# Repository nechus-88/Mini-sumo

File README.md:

# VELOCISTA #
Un velocista realizado para competir en la LNR

# Este cuenta con: # 
* 1-Moodulo de TB6612FNG
* 1-Esp-32 38 pines
* 1-Motores N20 2000RPM 
* 1-Sensores qtr8a
* 1-Sensores sharp GP2Y0A02YK0F 20-150cm
* 1-Bateria 2S 7.4v 350mAh LiPo

# Dimensiones: #
* 70 X 120 (ancho x largo )

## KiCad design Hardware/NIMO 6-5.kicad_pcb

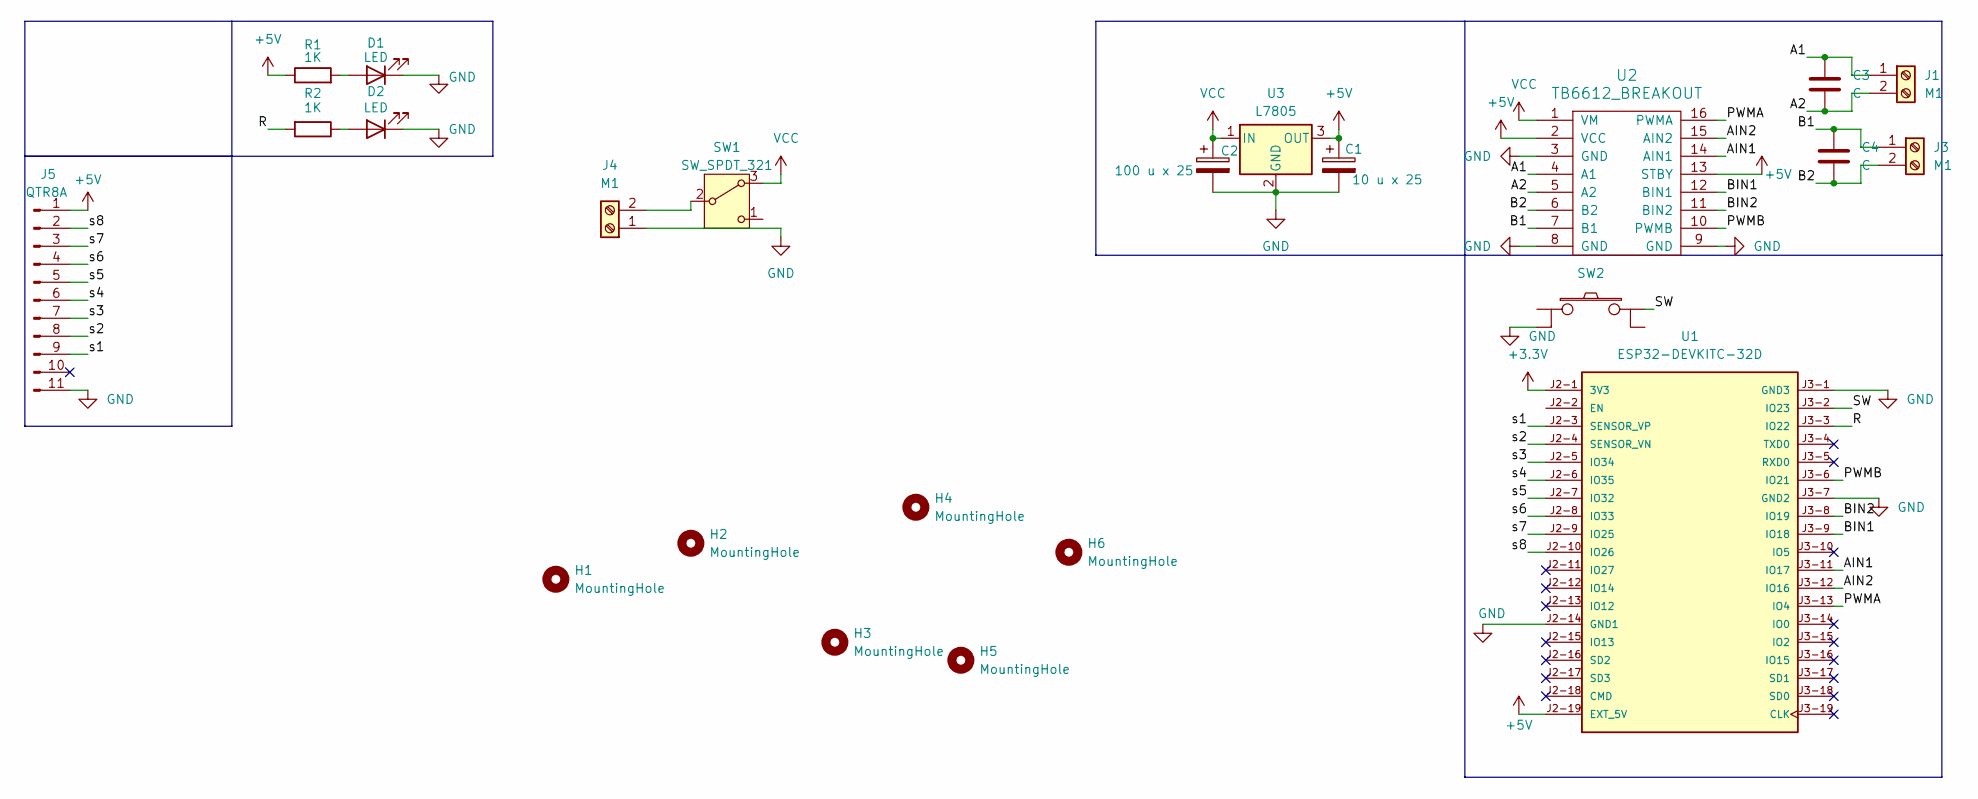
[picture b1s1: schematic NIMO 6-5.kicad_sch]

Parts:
C1: 10 u x 25; CP_Elec_8x6.2
C2: 100 u x 25; CP_Elec_6.3x5.4
C3, C4: C; C_0805_2012Metric
D1, D2: LED; LED_0805_2012Metric
H1, H2, H5, H6: MountingHole; MountingHole_3.2mm_M3
H3, H4: MountingHole; Pololu_Micro_Bracket_Wheel_42mms
J1, J3: M1; PinHeader_1x02_P2.54mm_Vertical
J4: M1; TerminalBlock_Altech_AK300-2_P5.00mm
J5: QTR8A; PinHeader_1x11_P2.54mm_Vertical
R1, R2: 1K; R_0805_2012Metric_Pad1.20x1.40mm_HandSolder
SW1: SW_SPDT_321; SW_SPDT_TH_Vertical
SW2: SW_PUSH; SW_PUSH_6mm_H5mm
U1: ESP32-DEVKITC-32D; MODULE_ESP32-DEVKITC-32D; PARTREV V4
U2: TB6612_BREAKOUT; TB6612_Breakout
U3: L7805; TO-263-2

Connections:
+3.3V: U1.J2-1 (3V3)
+5V: C1.1, J5.1, R1.1, U1.J2-19 (EXT_5V), U2.2 (VCC), U2.13 (STBY), U3.3 (OUT)
/A1: C3.2, J1.1, U2.4 (A1)
/A2: C3.1, J1.2, U2.5 (A2)
/AIN1: U1.J3-11 (IO17), U2.14 (AIN1)
/AIN2: U1.J3-12 (IO16), U2.15 (AIN2)
/B1: C4.2, J3.1, U2.7 (B1)
/B2: C4.1, J3.2, U2.6 (B2)
/BIN1: U1.J3-9 (IO18), U2.12 (BIN1)
/BIN2: U1.J3-8 (IO19), U2.11 (BIN2)
/PWMA: U1.J3-13 (IO4), U2.16 (PWMA)
/PWMB: U1.J3-6 (IO21), U2.10 (PWMB)
/R: R2.2, U1.J3-3 (IO22)
/SW: SW2.3, U1.J3-2 (IO23)
/s1: J5.9, U1.J2-3 (SENSOR_VP)
/s2: J5.8, U1.J2-4 (SENSOR_VN)
/s3: J5.7, U1.J2-5 (IO34)
/s4: J5.6, U1.J2-6 (IO35)
/s5: J5.5, U1.J2-7 (IO32)
/s6: J5.4, U1.J2-8 (IO33)
/s7: J5.3, U1.J2-9 (IO25)
/s8: J5.2, U1.J2-10 (IO26)
GND: C1.2, C2.2, D1.1 (K), D2.1 (K), J4.1, J5.11, SW2.2, U1.J2-14 (GND1), U1.J3-1 (GND3), U1.J3-7 (GND2), U2.3 (GND), U2.8 (GND), U2.9 (GND), U3.2 (GND)
unnamed: D1.2 (A), R1.2
unnamed: D2.2 (A), R2.1
unnamed: J4.2, SW1.2 (B)
VCC: C2.1, SW1.3 (A), U2.1 (VM), U3.1 (IN)

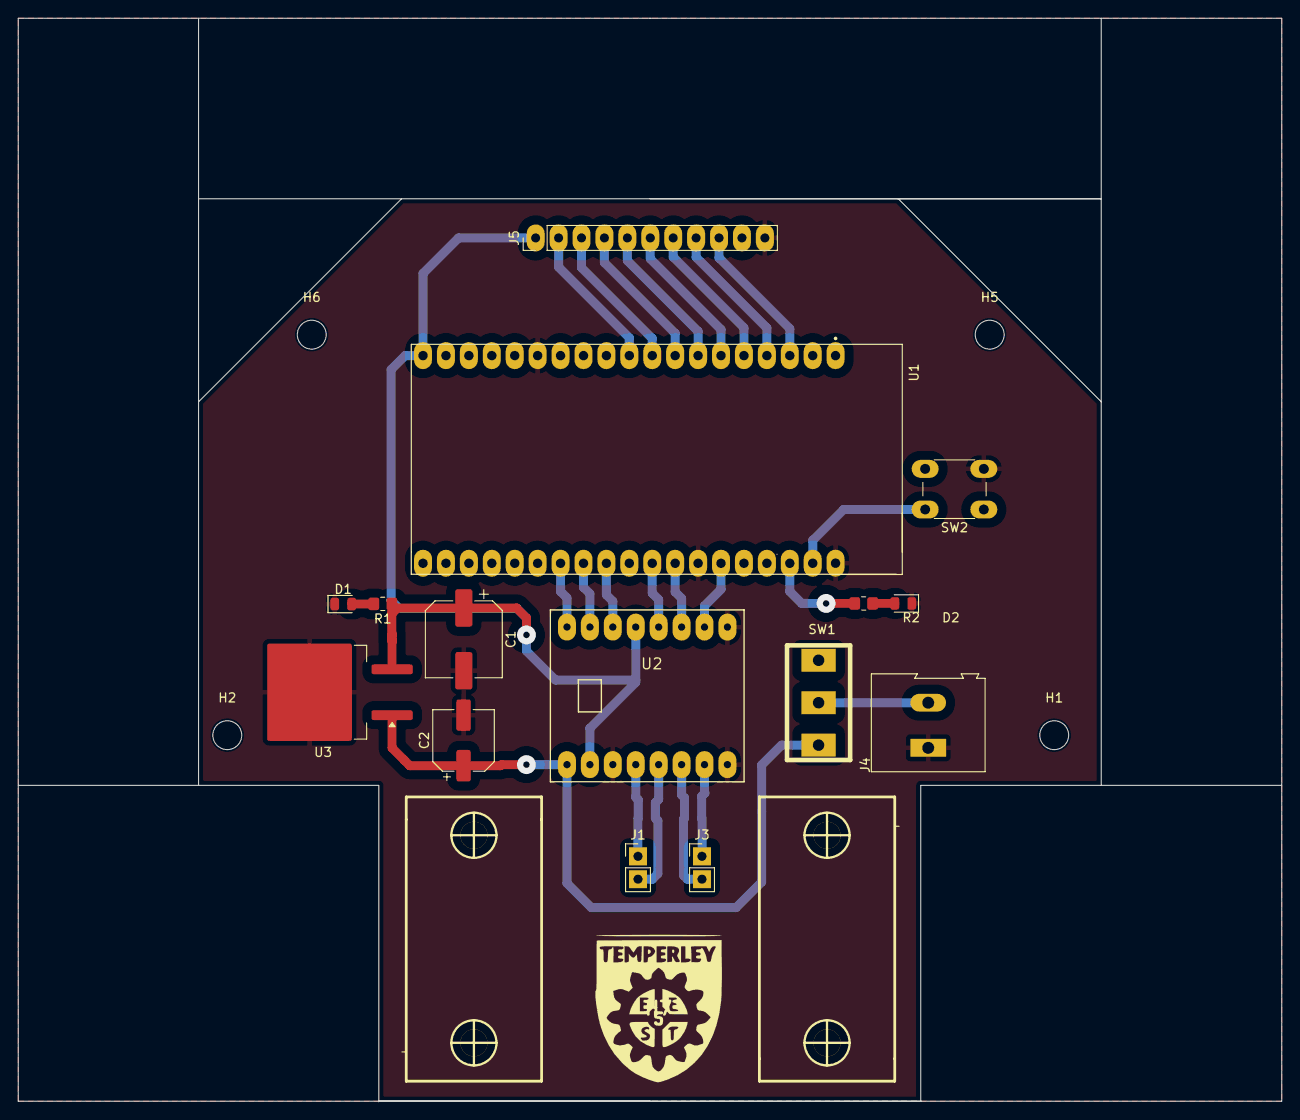
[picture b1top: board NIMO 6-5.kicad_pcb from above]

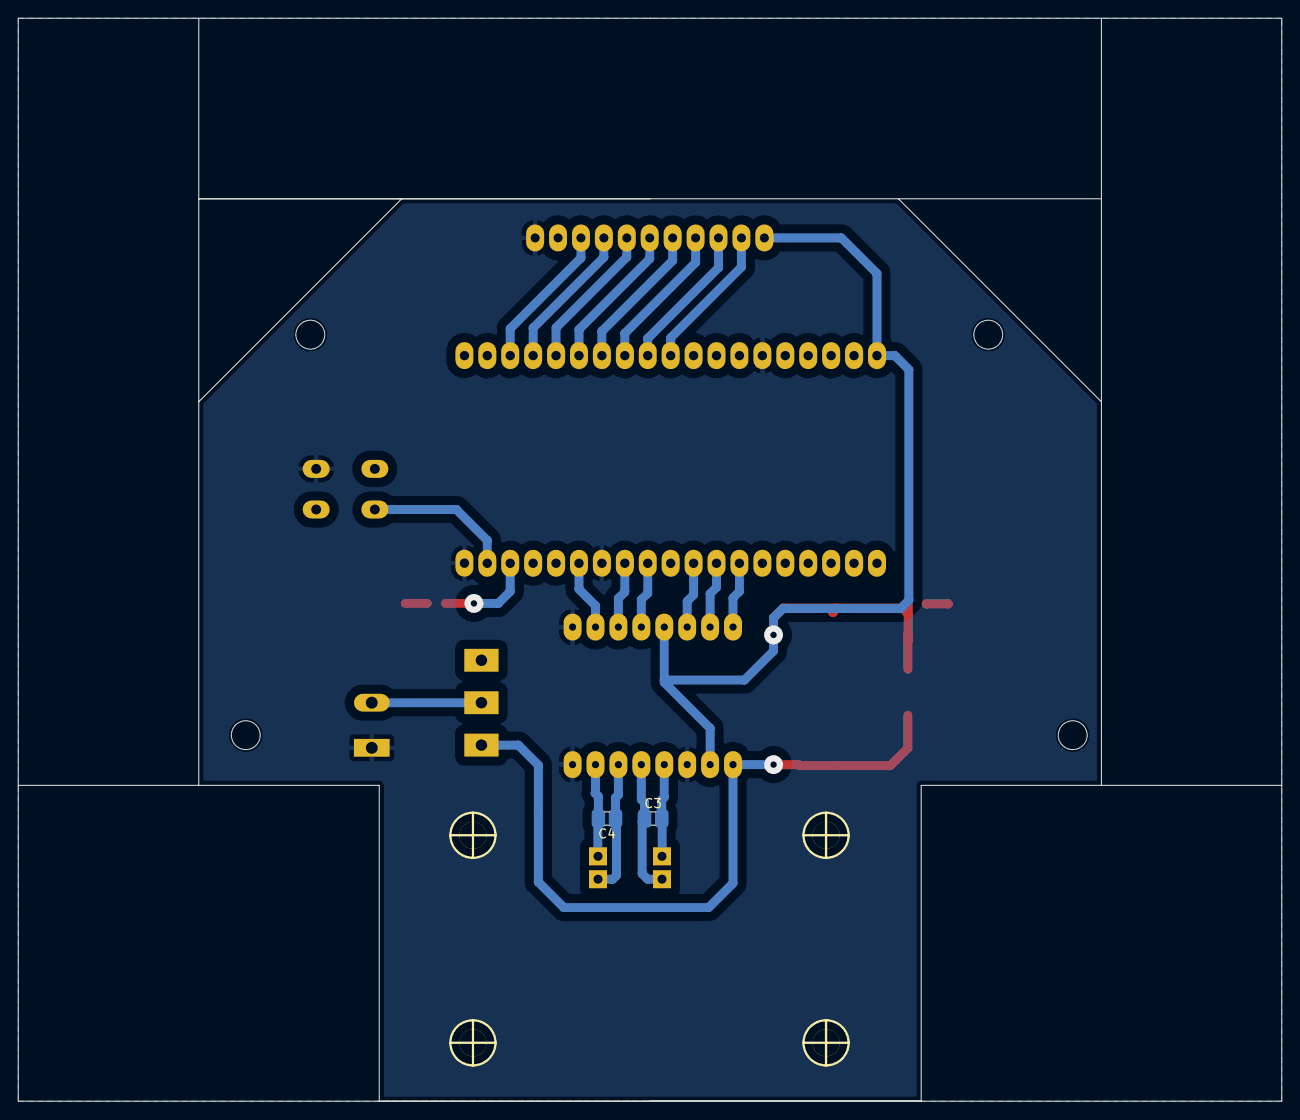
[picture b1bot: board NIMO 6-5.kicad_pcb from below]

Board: 2 copper layers, 140.0 x 120.0 mm, 24 parts (2 on the bottom side), 26 nets.

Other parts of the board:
H7: MountingHole; school

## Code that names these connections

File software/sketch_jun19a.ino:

#include <Arduino.h>
#include <QTRSensors.h>

#define NUM_SENSORS 8
uint8_t qtrPins[NUM_SENSORS] = {36, 39, 34, 35, 32, 33, 25, 26};
QTRSensors qtr;

#define BIN1 18
#define BIN2 19
#define AIN2 16
#define AIN1 17
#define PWMB 21
#define PWMA 4

#define LED_CALIBRACION 22
#define BOTON_CALIBRAR  23

#define PWM_FREQ  20000
#define PWM_RES   8
#define LINEA_NEGRA false

const int SETPOINT = 3500; // Centro de 8 sensores (0 a 7000)
float Kp = 0.32f;//0.31f
float Kd = 0.008f;//0.006f

float lastError = 0;
//float derivFiltrado = 0;
//const float ALPHA_D = 0.3f;

const int MAX_PWM       = 255;
const int VELOCIDAD_MAX = 255;
const int VELOCIDAD_MIN = 55;

unsigned long ultimoLoopUs = 0;

enum EstadoRobot { ESTADO_INICIAL, ESTADO_CALIBRANDO, ESTADO_LISTO, ESTADO_SIGUIENDO };
EstadoRobot estado = ESTADO_INICIAL;

void motorIzquierdo(int vel) {
  if (vel >= 0) { 
    digitalWrite(AIN1, LOW); 
  digitalWrite(AIN2, HIGH);
   }
  else { 
    digitalWrite(AIN1, HIGH);
     digitalWrite(AIN2, LOW);
      vel = -vel; }
  ledcWrite(PWMA, constrain(vel, 0, MAX_PWM));
}

void motorDerecho(int vel) {
  if (vel >= 0) {
     digitalWrite(BIN1, LOW);
      digitalWrite(BIN2, HIGH); 
      }
  else { 
    digitalWrite(BIN1, HIGH);
     digitalWrite(BIN2, LOW);
      vel = -vel;
       }
  ledcWrite(PWMB, constrain(vel, 0, MAX_PWM));
}

void motoresParar() {
  ledcWrite(PWMA, 0);
  ledcWrite(PWMB, 0);
}


void calibrar() {
  estado = ESTADO_CALIBRANDO;
  unsigned long tiempoInicio = millis();

  while (millis() - tiempoInicio < 12000) {
    qtr.calibrate();
    digitalWrite(LED_CALIBRACION, (millis() / 100) % 2); // Parpadeo
  }
  
  digitalWrite(LED_CALIBRACION, LOW);
  estado = ESTADO_LISTO;
  Serial.println("Calibración completa.");
}

void manejarBoton() {
  static bool presionadoPrev = HIGH;
  static unsigned long tiempoPresionado = 0;
  bool presionadoAct = digitalRead(BOTON_CALIBRAR);

  if (presionadoPrev == HIGH && presionadoAct == LOW) {
    tiempoPresionado = millis();
  }

  if (presionadoPrev == LOW && presionadoAct == HIGH) {
    unsigned long duracion = millis() - tiempoPresionado;

    if (duracion > 2000) { // +2s: Calibrar
      calibrar();
    } else if (duracion > 50) { // Click corto: Arrancar/Parar
      if (estado == ESTADO_LISTO) {
        estado = ESTADO_SIGUIENDO;
        ultimoLoopUs = micros();
        Serial.println("Robot Iniciado");
      } else if (estado == ESTADO_SIGUIENDO) {
        motoresParar();
        estado = ESTADO_LISTO;
        Serial.println("Robot Detenido");
      }
    }
  }
  presionadoPrev = presionadoAct;
}

void seguirLinea() {
  unsigned long ahoraUs = micros();
  float dt = (ahoraUs - ultimoLoopUs) / 1000000.0f;
  ultimoLoopUs = ahoraUs;
  if (dt > 0.1f) dt = 0.1f;

  uint16_t sensorValues[NUM_SENSORS];
  uint16_t position = LINEA_NEGRA ? qtr.readLineBlack(sensorValues) : qtr.readLineWhite(sensorValues);

  float error = (float)SETPOINT - (float)position;
  
  // PID (PD)
  float Errorderivativo = (error - lastError) / dt;
  //derivFiltrado = ALPHA_D * derivFiltrado + (1.0f - ALPHA_D) * derivRaw;
  float U = (Kp * error) + (Kd * Errorderivativo);
 lastError = error;
U = constrain(U, -255, 255);

int velIzq = VELOCIDAD_BASE + U;
int velDer = VELOCIDAD_BASE - U;
 
  motorIzquierdo(velIzq);
  motorDerecho(velDer);
}

void setup() {
  Serial.begin(115200);

  // Configuración Pines Motores
  pinMode(AIN1, OUTPUT);
   pinMode(AIN2, OUTPUT);
  pinMode(BIN1, OUTPUT);
   pinMode(BIN2, OUTPUT);
  
  // Configuración PWM moderna ESP32
  ledcAttach(PWMA, PWM_FREQ, PWM_RES);
  ledcAttach(PWMB, PWM_FREQ, PWM_RES);

  pinMode(LED_CALIBRACION, OUTPUT);
  pinMode(BOTON_CALIBRAR, INPUT_PULLUP);

  // Sensores
  qtr.setTypeAnalog();
  qtr.setSensorPins(qtrPins, NUM_SENSORS);

  Serial.println("Sistema iniciado. ESP32 listo.");
}

void loop() {
  manejarBoton();

  if (estado == ESTADO_SIGUIENDO) {
    seguirLinea();
  } else {
    motoresParar();
  }
}

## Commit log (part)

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2026-03-27 MI PRIMER COMMIT
2026-03-27 Modificamos Titulo en index.html
2026-03-27 carpetas
2026-04-13 Create Librerias
2026-04-13 Create Apartado para librerias
2026-04-21 PCB y Esqueamatico de kicad
    .
2026-05-11 cambio de placa
    .......
2026-05-12 cambio de placa
    12/5/26
2026-05-12 logo de la escuela
    12/5/26-13:36
